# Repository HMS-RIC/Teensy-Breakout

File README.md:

# Teensy-Breakout
Breakout board for 2x Teensys. Fits into 19" rack. Brings many IO pins to front panel BNC connectors. Includes solenoid drivers and comparator-based lick detection with fixed hysteresis.

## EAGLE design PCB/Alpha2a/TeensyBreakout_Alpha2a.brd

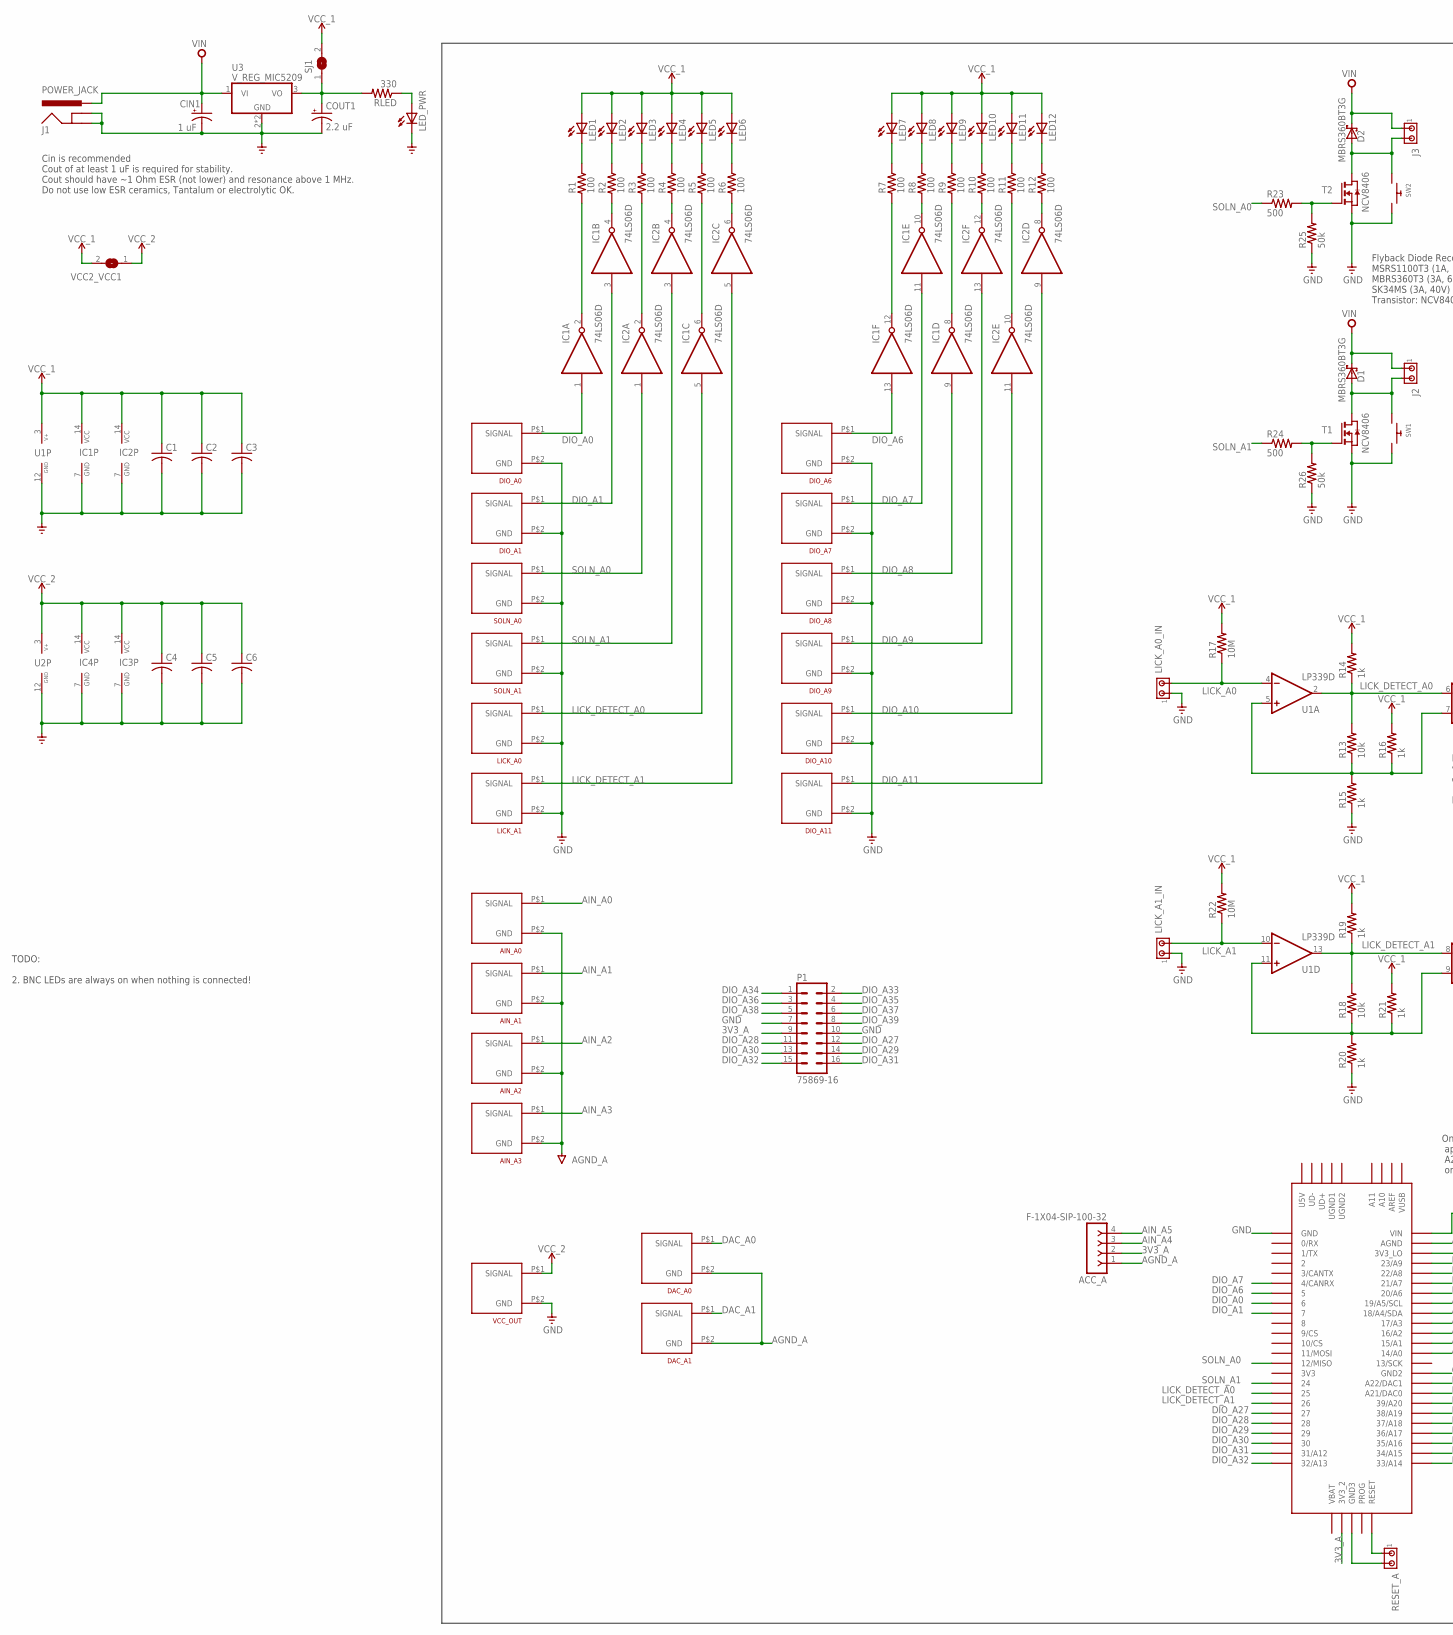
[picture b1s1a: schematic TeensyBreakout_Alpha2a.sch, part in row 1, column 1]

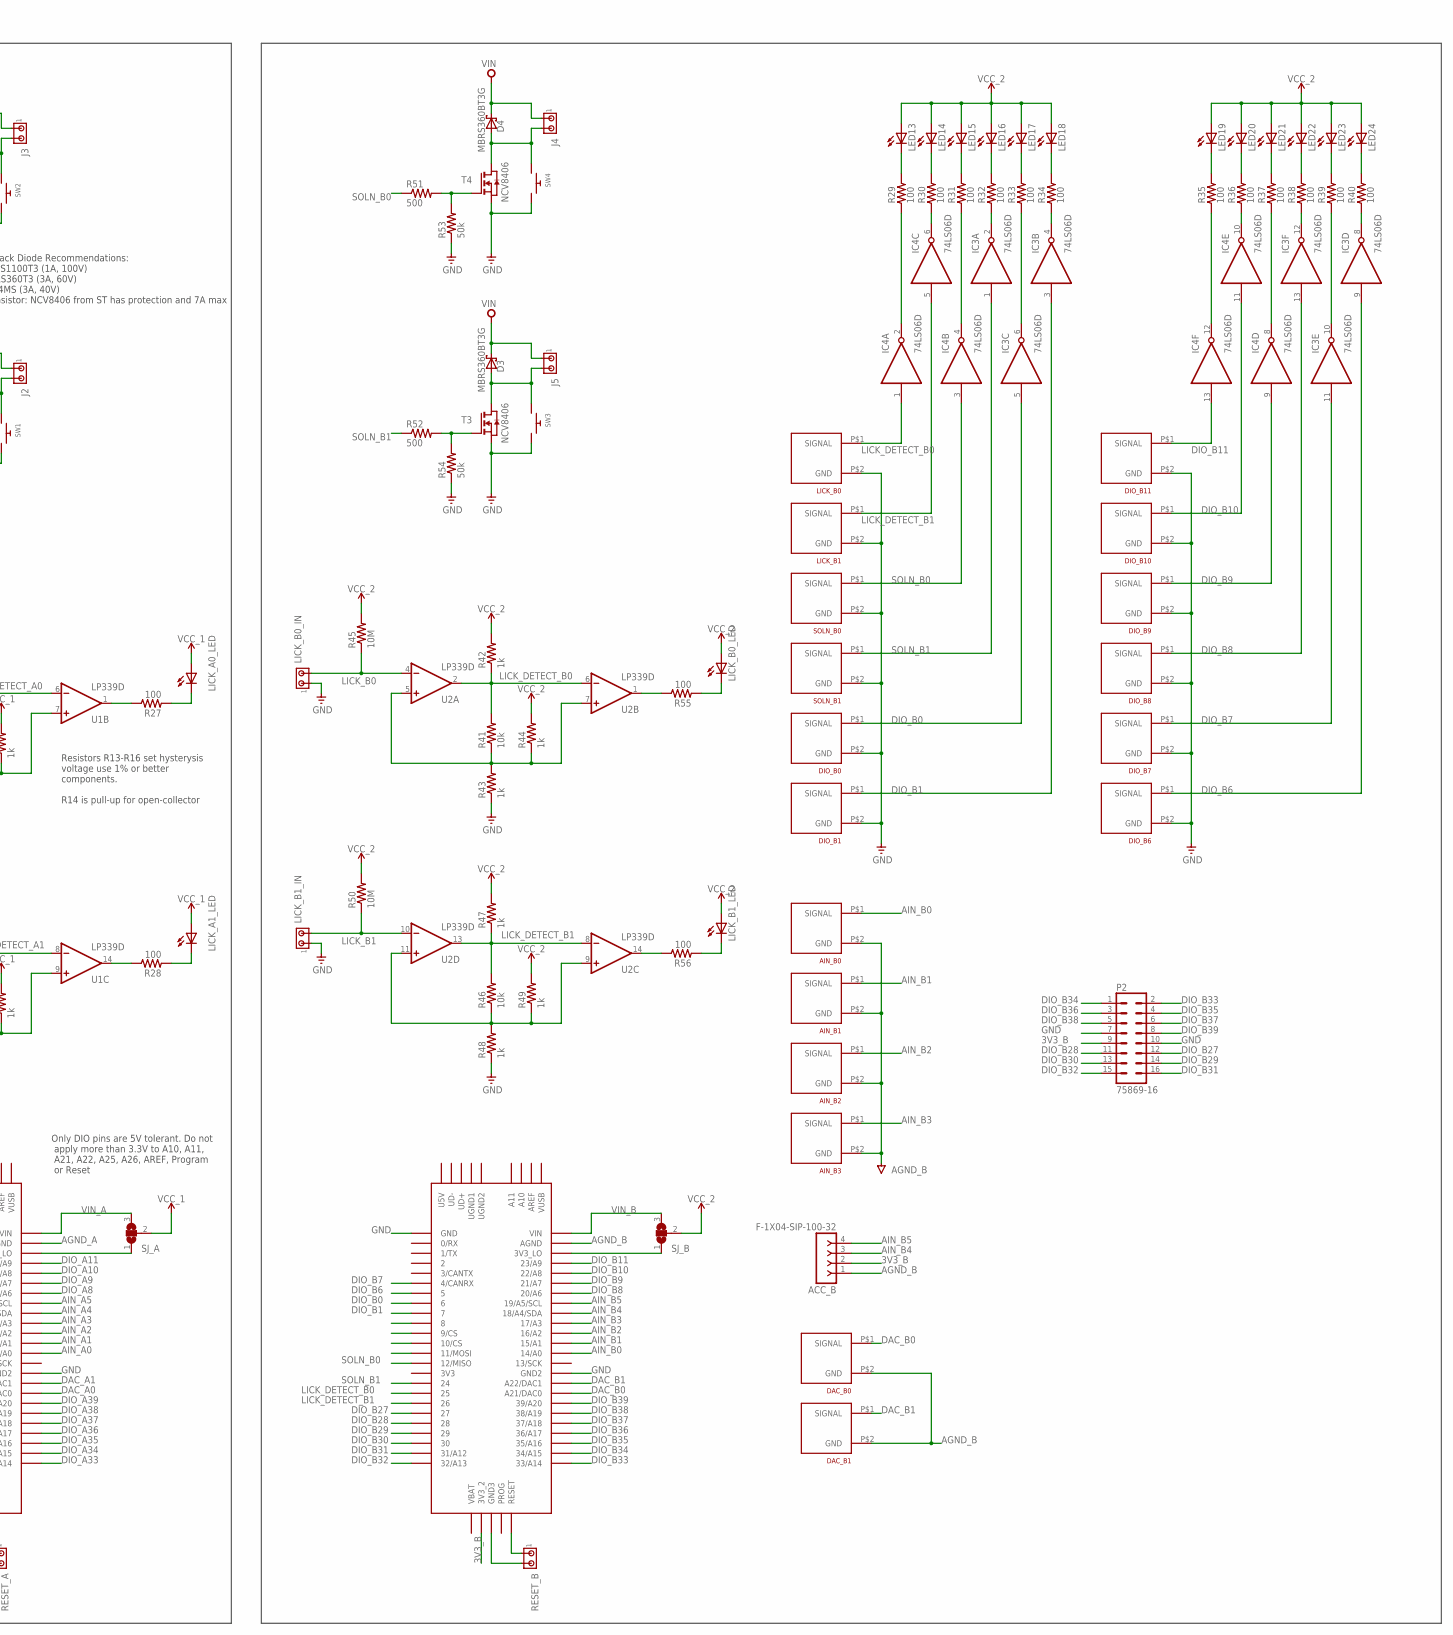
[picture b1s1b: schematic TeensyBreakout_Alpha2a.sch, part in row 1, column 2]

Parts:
ACC_A: F-1X04-SIP-100-32; SIP-100-04-32
ACC_B: F-1X04-SIP-100-32; SIP-100-04-32
AIN_A0, AIN_A1, AIN_A2, AIN_A3: BNC_VERTICAL
AIN_B0, AIN_B1, AIN_B2, AIN_B3: BNC_VERTICAL
C1, C2, C3, C4, C5, C6: C-USC0805K; C0805K
CIN1: 1 uF; E2,5-5
COUT1: 2.2 uF; E2,5-5
D1, D2, D3, D4: MBRS360BT3G; DIODE_SMB
DAC_A0, DAC_A1: BNC_VERTICAL
DAC_B0, DAC_B1: BNC_VERTICAL
DIO_A0, DIO_A1, DIO_A6, DIO_A7, DIO_A8, DIO_A9, DIO_A10, DIO_A11: BNC_VERTICAL
DIO_B0, DIO_B1, DIO_B6, DIO_B7, DIO_B8, DIO_B9, DIO_B10, DIO_B11: BNC_VERTICAL
IC1, IC2, IC3, IC4: 74LS06D; SO14
J1: POWER_JACK; POWER_JACK_PTH
J2, J3, J4, J5: MTA02-100; 10X02MTA
LED1, LED2, LED3, LED4, LED5, LED6, LED7, LED8, LED9, LED10, LED11, LED12, LED13, LED14, LED15, LED16, LED17, LED18, LED19, LED20, LED21, LED22, LED23, LED24: LED5MM
LED_PWR: LED5MM
LICK_A0, LICK_A1: BNC_VERTICAL
LICK_A0_IN, LICK_A1_IN: MTA02-100; 10X02MTA
LICK_A0_LED, LICK_A1_LED: LED5MM
LICK_B0, LICK_B1: BNC_VERTICAL
LICK_B0_IN, LICK_B1_IN: MTA02-100; 10X02MTA
LICK_B0_LED, LICK_B1_LED: LED5MM
P1, P2: 75869-16
R1, R2, R3, R4, R5, R6, R7, R8, R9, R10, R11, R12, R29, R30, R31, R32, R33, R34, R35, R36, R37, R38, R39, R40: 100; R1206MP
R13, R18, R41, R46: 10k; M0805
R14, R15, R16, R19, R20, R21, R42, R43, R44, R47, R48, R49: 1k; M0805
R17, R22, R45, R50: 10M; M0805
R23, R24, R51, R52: 500; M1206
R25, R26, R53, R54: 50k; M1206
R27, R28, R55, R56: 100; R1206
RESET_A: MTA02-100; 10X02MTA
RESET_B: MTA02-100; 10X02MTA
RLED: 330; R0805
SJ1: SJ
SJ_A: SJ2W; SJ_2
SJ_B: SJ2W; SJ_2
SOLN_A0, SOLN_A1: BNC_VERTICAL
SOLN_B0, SOLN_B1: BNC_VERTICAL
SW1, SW2, SW3, SW4: SWITCH_PUSHBUTTONEVQ-PE; TACT_PANA-EVQ
T1, T2, T3, T4: NCV8406; SOT223
TEENSY_A: TEENSY_3.5/3.6
TEENSY_B: TEENSY_3.5/3.6
U1, U2: LP339D; SO14
U3: V_REG_MIC5209; SOT-223
VCC2_VCC1: SJW
VCC_OUT: BNC_VERTICAL

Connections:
3V3_A: ACC_A.2, P1.9, TEENSY_A.3V3_2
3V3_B: ACC_B.2, P2.9, TEENSY_B.3V3_2
AGND_A: ACC_A.1, AIN_A0.P$2 (GND), AIN_A1.P$2 (GND), AIN_A2.P$2 (GND), AIN_A3.P$2 (GND), DAC_A0.P$2 (GND), DAC_A1.P$2 (GND), TEENSY_A.AGND
AGND_B: ACC_B.1, AIN_B0.P$2 (GND), AIN_B1.P$2 (GND), AIN_B2.P$2 (GND), AIN_B3.P$2 (GND), DAC_B0.P$2 (GND), DAC_B1.P$2 (GND), TEENSY_B.AGND
AIN_A0: AIN_A0.P$1 (SIGNAL), TEENSY_A.14/A0
AIN_A1: AIN_A1.P$1 (SIGNAL), TEENSY_A.15/A1
AIN_A2: AIN_A2.P$1 (SIGNAL), TEENSY_A.16/A2
AIN_A3: AIN_A3.P$1 (SIGNAL), TEENSY_A.17/A3
AIN_A4: ACC_A.3, TEENSY_A.18/A4/SDA
AIN_A5: ACC_A.4, TEENSY_A.19/A5/SCL
AIN_B0: AIN_B0.P$1 (SIGNAL), TEENSY_B.14/A0
AIN_B1: AIN_B1.P$1 (SIGNAL), TEENSY_B.15/A1
AIN_B2: AIN_B2.P$1 (SIGNAL), TEENSY_B.16/A2
AIN_B3: AIN_B3.P$1 (SIGNAL), TEENSY_B.17/A3
AIN_B4: ACC_B.3, TEENSY_B.18/A4/SDA
AIN_B5: ACC_B.4, TEENSY_B.19/A5/SCL
DAC_A0: DAC_A0.P$1 (SIGNAL), TEENSY_A.21/DAC0 (A21/DAC0)
DAC_A1: DAC_A1.P$1 (SIGNAL), TEENSY_A.A22/DAC1
DAC_B0: DAC_B0.P$1 (SIGNAL), TEENSY_B.21/DAC0 (A21/DAC0)
DAC_B1: DAC_B1.P$1 (SIGNAL), TEENSY_B.A22/DAC1
DIO_A0: DIO_A0.P$1 (SIGNAL), IC1.1 (I), TEENSY_A.6
DIO_A1: DIO_A1.P$1 (SIGNAL), IC1.3 (I), TEENSY_A.7
DIO_A6: DIO_A6.P$1 (SIGNAL), IC1.13 (I), TEENSY_A.5
DIO_A7: DIO_A7.P$1 (SIGNAL), IC1.11 (I), TEENSY_A.4/CANRX
DIO_A8: DIO_A8.P$1 (SIGNAL), IC1.9 (I), TEENSY_A.20/A6
DIO_A9: DIO_A9.P$1 (SIGNAL), IC2.13 (I), TEENSY_A.21/A7
DIO_A10: DIO_A10.P$1 (SIGNAL), IC2.11 (I), TEENSY_A.22/A8
DIO_A11: DIO_A11.P$1 (SIGNAL), IC2.9 (I), TEENSY_A.23/A9
DIO_A27: P1.12, TEENSY_A.27
DIO_A28: P1.11, TEENSY_A.28
DIO_A29: P1.14, TEENSY_A.29
DIO_A30: P1.13, TEENSY_A.30
DIO_A31: P1.16, TEENSY_A.31/A12
DIO_A32: P1.15, TEENSY_A.32/A13
DIO_A33: P1.2, TEENSY_A.33/A14
DIO_A34: P1.1, TEENSY_A.34/A15
DIO_A35: P1.4, TEENSY_A.35/A16
DIO_A36: P1.3, TEENSY_A.36/A17
DIO_A37: P1.6, TEENSY_A.37/A18
DIO_A38: P1.5, TEENSY_A.38/A19
DIO_A39: P1.8, TEENSY_A.39/A20
DIO_B0: DIO_B0.P$1 (SIGNAL), IC3.5 (I), TEENSY_B.6
DIO_B1: DIO_B1.P$1 (SIGNAL), IC3.3 (I), TEENSY_B.7
DIO_B6: DIO_B6.P$1 (SIGNAL), IC3.9 (I), TEENSY_B.5
DIO_B7: DIO_B7.P$1 (SIGNAL), IC3.11 (I), TEENSY_B.4/CANRX
DIO_B8: DIO_B8.P$1 (SIGNAL), IC3.13 (I), TEENSY_B.20/A6
DIO_B9: DIO_B9.P$1 (SIGNAL), IC4.9 (I), TEENSY_B.21/A7
DIO_B10: DIO_B10.P$1 (SIGNAL), IC4.11 (I), TEENSY_B.22/A8
DIO_B11: DIO_B11.P$1 (SIGNAL), IC4.13 (I), TEENSY_B.23/A9
DIO_B27: P2.12, TEENSY_B.27
DIO_B28: P2.11, TEENSY_B.28
DIO_B29: P2.14, TEENSY_B.29
DIO_B30: P2.13, TEENSY_B.30
DIO_B31: P2.16, TEENSY_B.31/A12
DIO_B32: P2.15, TEENSY_B.32/A13
DIO_B33: P2.2, TEENSY_B.33/A14
DIO_B34: P2.1, TEENSY_B.34/A15
DIO_B35: P2.4, TEENSY_B.35/A16
DIO_B36: P2.3, TEENSY_B.36/A17
DIO_B37: P2.6, TEENSY_B.37/A18
DIO_B38: P2.5, TEENSY_B.38/A19
DIO_B39: P2.8, TEENSY_B.39/A20
GND: C1.2, C2.2, C3.2, C4.2, C5.2, C6.2, CIN1.-, COUT1.-, DIO_A0.P$2 (GND), DIO_A1.P$2 (GND), DIO_A6.P$2 (GND), DIO_A7.P$2 (GND), DIO_A8.P$2 (GND), DIO_A9.P$2 (GND), DIO_A10.P$2 (GND), DIO_A11.P$2 (GND), DIO_B0.P$2 (GND), DIO_B1.P$2 (GND), DIO_B6.P$2 (GND), DIO_B7.P$2 (GND), DIO_B8.P$2 (GND), DIO_B9.P$2 (GND), DIO_B10.P$2 (GND), DIO_B11.P$2 (GND), IC1.7 (GND), IC2.7 (GND), IC3.7 (GND), IC4.7 (GND), J1.GND, J1.GNDBREAK, LED_PWR.K (C), LICK_A0.P$2 (GND), LICK_A0_IN.1, LICK_A1.P$2 (GND), LICK_A1_IN.1, LICK_B0.P$2 (GND), LICK_B0_IN.1, LICK_B1.P$2 (GND), LICK_B1_IN.1, P1.7, P1.10, P2.7, P2.10, R15.1, R20.1, R25.1, R26.1, R43.1, R48.1, R53.1, R54.1, RESET_A.2, RESET_B.2, SOLN_A0.P$2 (GND), SOLN_A1.P$2 (GND), SOLN_B0.P$2 (GND), SOLN_B1.P$2 (GND), SW1.P$2, SW2.P$2, SW3.P$2, SW4.P$2, T1.3 (S), T2.3 (S), T3.3 (S), T4.3 (S), TEENSY_A.GND, TEENSY_A.GND2, TEENSY_A.GND3, TEENSY_B.GND, TEENSY_B.GND2, TEENSY_B.GND3, U1.12 (GND), U2.12 (GND), U3.2 (GND), U3.4 (GND), VCC_OUT.P$2 (GND)
LICK_A0: LICK_A0_IN.2, R17.1, U1.4 (-IN)
LICK_A1: LICK_A1_IN.2, R22.1, U1.10 (-IN)
LICK_B0: LICK_B0_IN.2, R45.1, U2.4 (-IN)
LICK_B1: LICK_B1_IN.2, R50.1, U2.10 (-IN)
LICK_DETECT_A0: IC1.5 (I), LICK_A0.P$1 (SIGNAL), R13.2, R14.1, TEENSY_A.25, U1.2 (OUT), U1.6 (-IN)
LICK_DETECT_A1: IC2.5 (I), LICK_A1.P$1 (SIGNAL), R18.2, R19.1, TEENSY_A.26, U1.8 (-IN), U1.13 (OUT)
LICK_DETECT_B0: IC4.1 (I), LICK_B0.P$1 (SIGNAL), R41.2, R42.1, TEENSY_B.25, U2.2 (OUT), U2.6 (-IN)
LICK_DETECT_B1: IC4.5 (I), LICK_B1.P$1 (SIGNAL), R46.2, R47.1, TEENSY_B.26, U2.8 (-IN), U2.13 (OUT)
unnamed: IC1.2 (O), R1.1
unnamed: IC1.4 (O), R2.1
unnamed: IC2.4 (O), R4.1
unnamed: IC2.2 (O), R3.1
unnamed: IC1.6 (O), R5.1
unnamed: IC2.6 (O), R6.1
unnamed: LED1.K (C), R1.2
unnamed: LED2.K (C), R2.2
unnamed: LED3.K (C), R3.2
unnamed: LED4.K (C), R4.2
unnamed: LED5.K (C), R5.2
unnamed: LED6.K (C), R6.2
unnamed: R18.1, R20.2, R21.1, U1.9 (+IN), U1.11 (+IN)
unnamed: LED_PWR.A, RLED.1
unnamed: IC1.12 (O), R7.1
unnamed: IC1.10 (O), R8.1
unnamed: IC1.8 (O), R9.1
unnamed: IC2.12 (O), R10.1
unnamed: IC2.10 (O), R11.1
unnamed: IC2.8 (O), R12.1
unnamed: LED7.K (C), R7.2
unnamed: LED8.K (C), R8.2
unnamed: LED9.K (C), R9.2
unnamed: LED10.K (C), R10.2
unnamed: LED11.K (C), R11.2
unnamed: LED12.K (C), R12.2
unnamed: R13.1, R15.2, R16.1, U1.5 (+IN), U1.7 (+IN)
unnamed: SJ_A.1, TEENSY_A.3V3_LO
unnamed: COUT1.+, RLED.2, SJ1.1, U3.3 (VO)
unnamed: R23.2, R25.2, T2.1 (G)
unnamed: R27.2, U1.1 (OUT)
unnamed: R24.2, R26.2, T1.1 (G)
unnamed: LICK_A0_LED.K (C), R27.1
unnamed: IC4.4 (O), R31.1
unnamed: IC4.6 (O), R30.1
unnamed: IC3.6 (O), R33.1
unnamed: LICK_A1_LED.K (C), R28.1
unnamed: IC3.4 (O), R34.1
unnamed: R28.2, U1.14 (OUT)
unnamed: SJ_B.1, TEENSY_B.3V3_LO
unnamed: IC3.2 (O), R32.1
unnamed: LED14.K (C), R30.2
unnamed: LED15.K (C), R31.2
unnamed: LED16.K (C), R32.2
unnamed: LED17.K (C), R33.2
unnamed: LED18.K (C), R34.2
unnamed: IC4.12 (O), R35.1
unnamed: IC4.10 (O), R36.1
unnamed: IC4.8 (O), R37.1
unnamed: IC3.12 (O), R38.1
unnamed: IC3.10 (O), R39.1
unnamed: IC3.8 (O), R40.1
unnamed: LED19.K (C), R35.2
unnamed: LED20.K (C), R36.2
unnamed: LED21.K (C), R37.2
unnamed: LED22.K (C), R38.2
unnamed: LED23.K (C), R39.2
unnamed: LED24.K (C), R40.2
unnamed: R51.2, R53.2, T4.1 (G)
unnamed: R52.2, R54.2, T3.1 (G)
unnamed: IC4.2 (O), R29.1
unnamed: LED13.K (C), R29.2
unnamed: R41.1, R43.2, R44.1, U2.5 (+IN), U2.7 (+IN)
unnamed: R46.1, R48.2, R49.1, U2.9 (+IN), U2.11 (+IN)
unnamed: R55.2, U2.1 (OUT)
unnamed: LICK_B0_LED.K (C), R55.1
unnamed: LICK_B1_LED.K (C), R56.1
unnamed: R56.2, U2.14 (OUT)
RESET_A: RESET_A.1, TEENSY_A.RESET
RESET_B: RESET_B.1, TEENSY_B.RESET
SOLN_A0: IC2.1 (I), R23.1, SOLN_A0.P$1 (SIGNAL), TEENSY_A.12/MISO
SOLN_A1: IC2.3 (I), R24.1, SOLN_A1.P$1 (SIGNAL), TEENSY_A.24
SOLN_B0: IC4.3 (I), R51.1, SOLN_B0.P$1 (SIGNAL), TEENSY_B.12/MISO
SOLN_B1: IC3.1 (I), R52.1, SOLN_B1.P$1 (SIGNAL), TEENSY_B.24
VCC_1: C1.1, C2.1, C3.1, IC1.14 (VCC), IC2.14 (VCC), LED1.A, LED2.A, LED3.A, LED4.A, LED5.A, LED6.A, LED7.A, LED8.A, LED9.A, LED10.A, LED11.A, LED12.A, LICK_A0_LED.A, LICK_A1_LED.A, R14.2, R16.2, R17.2, R19.2, R21.2, R22.2, SJ1.2, SJ_A.2, U1.3 (V+), VCC2_VCC1.2
VCC_2: C4.1, C5.1, C6.1, IC3.14 (VCC), IC4.14 (VCC), LED13.A, LED14.A, LED15.A, LED16.A, LED17.A, LED18.A, LED19.A, LED20.A, LED21.A, LED22.A, LED23.A, LED24.A, LICK_B0_LED.A, LICK_B1_LED.A, R42.2, R44.2, R45.2, R47.2, R49.2, R50.2, SJ_B.2, U2.3 (V+), VCC2_VCC1.1, VCC_OUT.P$1 (SIGNAL)
VIN: CIN1.+, D1.C (A), D2.C (A), D3.C (A), D4.C (A), J1.PWR, J2.1, J3.1, J4.1, J5.1, U3.1 (VI)
VIN_A: SJ_A.3, TEENSY_A.VIN
VIN_B: SJ_B.3, TEENSY_B.VIN
VOUT-2: D1.A (C), J2.2, SW1.P$1, T1.2 (D), T1.4 (D)
VOUT-3: D2.A (C), J3.2, SW2.P$1, T2.2 (D), T2.4 (D)
VOUT-5: D4.A (C), J4.2, SW4.P$1, T4.2 (D), T4.4 (D)
VOUT-6: D3.A (C), J5.2, SW3.P$1, T3.2 (D), T3.4 (D)

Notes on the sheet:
Cin is recommended Cout of at least 1 uF is required for stability. Cout should have ~1 Ohm ESR (not lower) and resonance above 1 MHz. Do not use low ESR ceramics, Tantalum or electrolytic OK.
Flyback Diode Recommendations: MSRS1100T3 (1A, 100V) MBRS360T3 (3A, 60V) SK34MS (3A, 40V) Transistor: NCV8406 from ST has protection and 7A max
Resistors R13-R16 set hysterysis voltage use 1% or better components. R14 is pull-up for open-collector
Only DIO pins are 5V tolerant. Do not apply more than 3.3V to A10, A11, A21, A22, A25, A26, AREF, Program or Reset
TODO: 2. BNC LEDs are always on when nothing is connected!

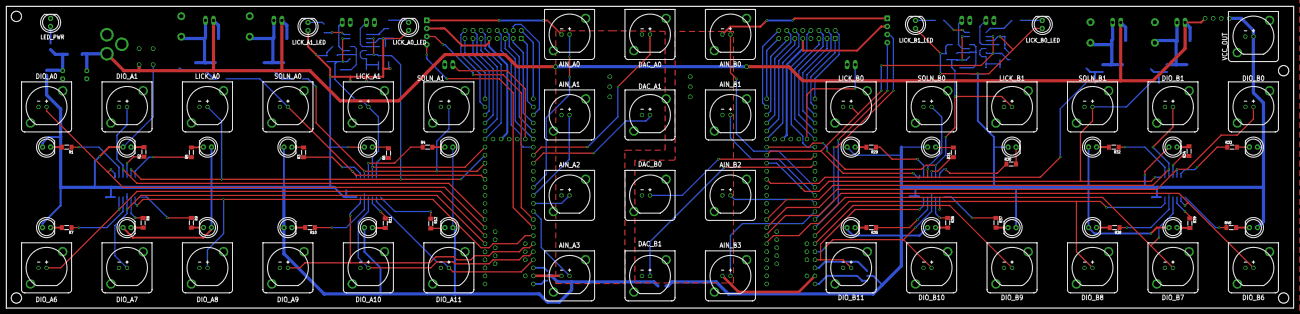
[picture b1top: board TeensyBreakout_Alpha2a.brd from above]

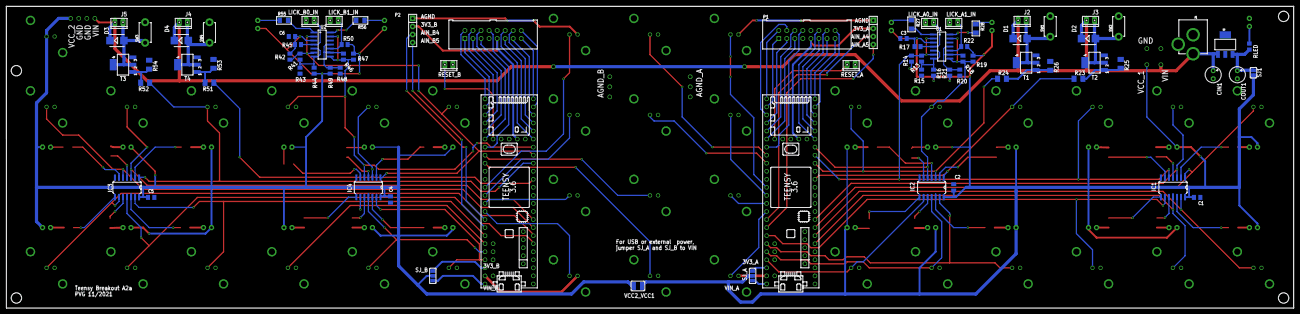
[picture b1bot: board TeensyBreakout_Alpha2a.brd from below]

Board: 2 copper layers, 406.4 x 95.2 mm, 171 parts (81 on the bottom side), 154 nets.

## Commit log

2021-09-02 Create test
2024-10-18 Create temp

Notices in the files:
parts and their libraries:
SparkFun-Connectors: Licensing: Creative Commons ShareAlike 4.0 International - https://creativecommons.org/licenses/by-sa/4.0
rc-master: Copyright (C) 2007-2008, Bob Starr
op-amp: Copyright (C) 2015, Bob Starr
con-fci-quickie: Copyright (C) 2008, Bob Starr
